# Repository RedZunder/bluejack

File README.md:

# bluejack
 Audio jack (3.5mm) to Bluetooth device

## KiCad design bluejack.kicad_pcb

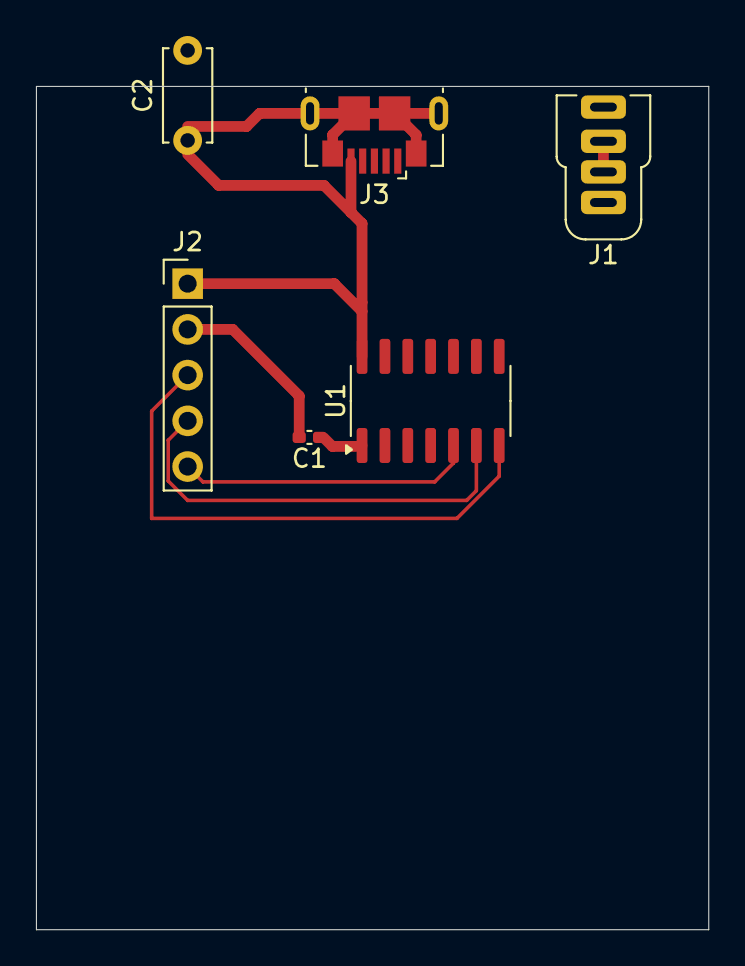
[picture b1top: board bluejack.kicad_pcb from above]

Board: 4 copper layers, 37.3 x 46.8 mm, 6 parts (0 on the bottom side), 7 nets.

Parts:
C1: 10n; C_0402_1005Metric_Pad0.74x0.62mm_HandSolder
C2: 100n; C_Disc_D5.0mm_W2.5mm_P5.00mm
J1: AudioPlug2; Plug_3.5mm_CUI_SP-3541
J2: BLE HC-08; PinHeader_1x05_P2.54mm_Vertical
J3: USB_B_Micro; USB_Micro-B_GCT_USB3076-30-A
U1: ATtiny814-SS; SOIC-14_3.9x8.7mm_P1.27mm

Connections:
+3V3: C1.2, J2.2
BLE_RX: J2.3, U1.7 (PB2)
BLE_TX: J2.4, U1.6 (PB3)
DIG: J2.5, U1.5 (PA7)
GND: C2.1, J2.1, J3.4 (ID), J3.5 (GND), U1.14 (GND)
unnamed: C2.2, J3.6 (Shield)
unnamed: C1.1, U1.1 (VCC)

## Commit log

2025-04-19 First ideas
